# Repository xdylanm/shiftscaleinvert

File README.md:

# Shift Scale Invert (SSI)

A 4HP module for signal offsets and scaling.

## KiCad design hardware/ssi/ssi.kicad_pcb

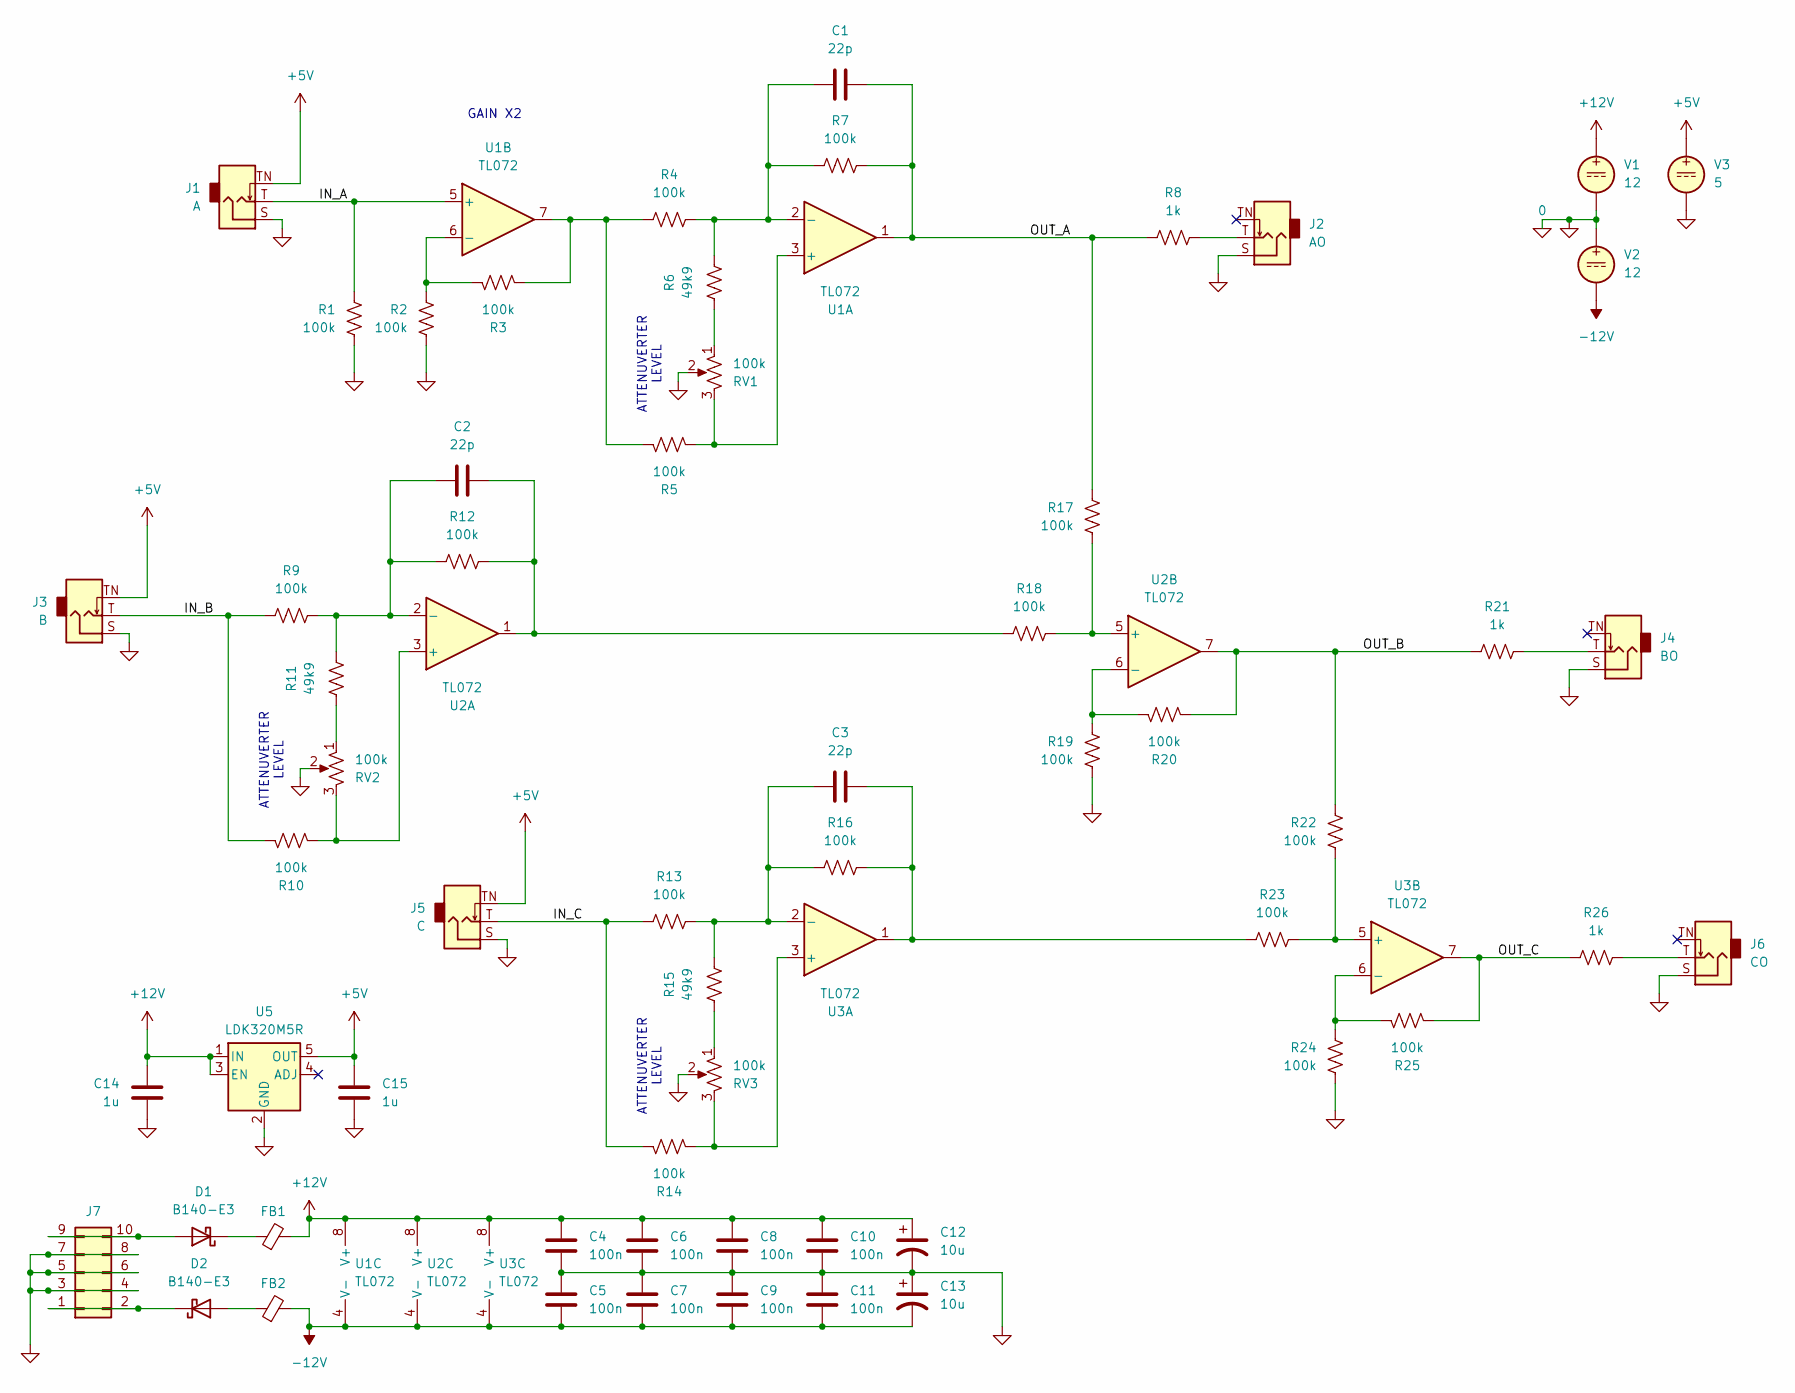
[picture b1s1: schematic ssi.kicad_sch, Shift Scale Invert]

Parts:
C1, C2, C3: 22p; C_0805_2012Metric_Pad1.18x1.45mm_HandSolder
C4, C5, C6, C7, C8, C9, C10, C11: 100n; C_0805_2012Metric_Pad1.18x1.45mm_HandSolder
C12, C13: 10u; CP_Radial_D5.0mm_P2.00mm
C14, C15: 1u; C_0805_2012Metric_Pad1.18x1.45mm_HandSolder
D1, D2: B140-E3; D_SMA
FB1, FB2: FerriteBead_Small; L_0805_2012Metric_Pad1.05x1.20mm_HandSolder
J1: A; Jack_3.5mm_QingPu_WQP-PJ301M-12_Vertical_Slim
J2: AO; Jack_3.5mm_QingPu_WQP-PJ301M-12_Vertical_Slim
J3: B; Jack_3.5mm_QingPu_WQP-PJ301M-12_Vertical_Slim
J4: BO; Jack_3.5mm_QingPu_WQP-PJ301M-12_Vertical_Slim
J5: C; Jack_3.5mm_QingPu_WQP-PJ301M-12_Vertical_Slim
J6: CO; Jack_3.5mm_QingPu_WQP-PJ301M-12_Vertical_Slim
J7: Conn_02x05_Odd_Even; IDC-Header_2x05_P2.54mm_Vertical
R1, R2, R3, R4, R5, R7, R9, R10, R12, R13, R14, R16, R17, R18, R19, R20, R22, R23, R24, R25: 100k; R_0805_2012Metric_Pad1.20x1.40mm_HandSolder
R6, R11, R15: 49k9; R_0805_2012Metric_Pad1.20x1.40mm_HandSolder
R8, R21, R26: 1k; R_0805_2012Metric_Pad1.20x1.40mm_HandSolder
RV1, RV2, RV3: 100k; Potentiometer_Bourns_PTV09A-1_Single_Vertical_thin
U1, U2, U3: TL072; SOIC-8_3.9x4.9mm_P1.27mm
U5: LDK320M5R; SOT-23-5_HandSoldering
V1, V2: 12
V3: 5

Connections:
0: C4.2, C5.1, C6.2, C7.1, C8.2, C9.1, C10.2, C11.1, C12.2, C13.1, C14.2, C15.2, J1.S, J2.S, J3.S, J4.S, J5.S, J6.S, J7.3, J7.4, J7.5, J7.6, J7.7, J7.8, R1.2, R2.2, R19.2, R24.2, RV1.2, RV1.MP, RV2.2, RV2.MP, RV3.2, RV3.MP, U5.2 (GND), V1.2, V2.1, V3.2
+5V: C15.1, J1.TN, J3.TN, J5.TN, U5.5 (OUT), V3.1
+12V: C4.1, C6.1, C8.1, C10.1, C12.1, C14.1, FB1.2, U1.8 (V+), U2.8 (V+), U3.8 (V+), U5.1 (IN), U5.3 (EN), V1.1
-12V: C5.2, C7.2, C9.2, C11.2, C13.2, FB2.2, U1.4 (V-), U2.4 (V-), U3.4 (V-), V2.2
/IN_A: J1.T, R1.1, U1.5 (+)
/IN_B: J3.T, R9.1, R10.1
/IN_C: J5.T, R13.1, R14.1
/OUT_A: C1.2, R7.2, R8.1, R17.1, U1.1
/OUT_B: R20.2, R21.1, R22.1, U2.7
/OUT_C: R25.2, R26.1, U3.7
unnamed: C2.2, R12.2, R18.1, U2.1
unnamed: C3.2, R16.2, R23.1, U3.1
unnamed: D1.2 (A), J7.9, J7.10
unnamed: D1.1 (K), FB1.1
unnamed: D2.2 (A), FB2.1
unnamed: D2.1 (K), J7.1, J7.2
unnamed: J2.T, R8.2
unnamed: J4.T, R21.2
unnamed: J6.T, R26.2
unnamed: R3.2, R4.1, R5.1, U1.7
unnamed: R6.1, RV1.1
unnamed: R11.1, RV2.1
unnamed: R15.1, RV3.1
unnamed: R5.2, RV1.3, U1.3 (+)
unnamed: C1.1, R4.2, R6.2, R7.1, U1.2 (-)
unnamed: R2.1, R3.1, U1.6 (-)
unnamed: R10.2, RV2.3, U2.3 (+)
unnamed: C2.1, R9.2, R11.2, R12.1, U2.2 (-)
unnamed: R17.2, R18.2, U2.5 (+)
unnamed: R19.1, R20.1, U2.6 (-)
unnamed: R14.2, RV3.3, U3.3 (+)
unnamed: C3.1, R13.2, R15.2, R16.1, U3.2 (-)
unnamed: R22.2, R23.2, U3.5 (+)
unnamed: R24.1, R25.1, U3.6 (-)

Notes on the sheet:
ATTENUVERTER LEVEL
GAIN X2

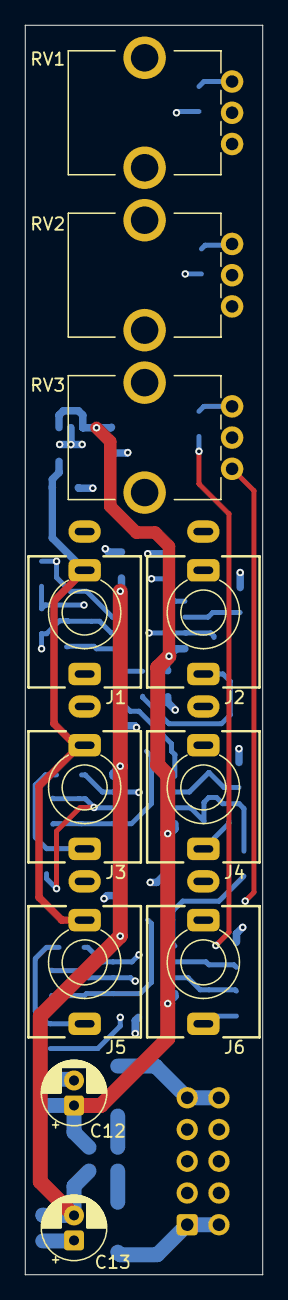
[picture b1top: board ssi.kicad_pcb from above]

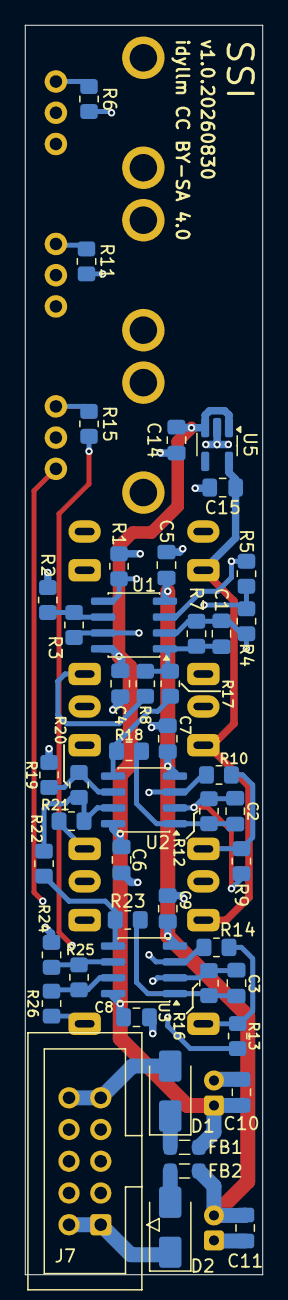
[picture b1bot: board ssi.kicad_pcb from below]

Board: 4 copper layers, 19.0 x 100.0 mm, 59 parts (48 on the bottom side), 34 nets.

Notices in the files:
hardware/ssi/ssi.kicad_pcb:
CC BY-SA 4.0
idyllm CC BY-SA 4.0
